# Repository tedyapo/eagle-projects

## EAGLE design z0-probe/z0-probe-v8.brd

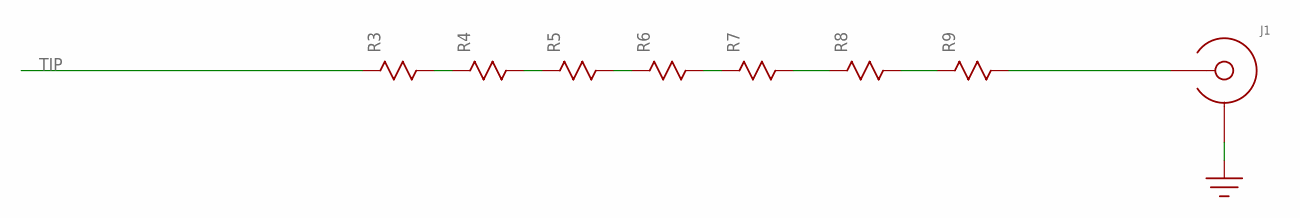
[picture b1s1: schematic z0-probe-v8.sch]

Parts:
J1: SMA-EDGE-LAUNCH; SMA_EDGE_LAUNCH_2L_4020_TAPER_FIXED
R3, R4, R5, R6, R7, R8, R9: R0603-TIGHT; 0603_TIGHT

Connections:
GND: J1.BOTTOM_GND (SHIELD), J1.GND@1 (SHIELD), J1.GND@2 (SHIELD), J1.GND@3 (SHIELD), J1.GND@4 (SHIELD), J1.GND@5 (SHIELD), J1.GND@6 (SHIELD), J1.GND@7 (SHIELD), J1.GND@8 (SHIELD), J1.GND@14 (SHIELD), J1.GND@15 (SHIELD), J1.GND@16 (SHIELD), J1.GND@17 (SHIELD), J1.GND_PAD1 (SHIELD), J1.GND_PAD2 (SHIELD), J1.P$1 (SHIELD), J1.P$2 (SHIELD)
unnamed: R3.P$2, R4.P$1
unnamed: R4.P$2, R5.P$1
unnamed: R5.P$2, R6.P$1
unnamed: R6.P$2, R7.P$1
unnamed: R7.P$2, R8.P$1
unnamed: R8.P$2, R9.P$1
unnamed: J1.CENTER@1 (CENTER), J1.P$3 (CENTER), R9.P$2
TIP: R3.P$1

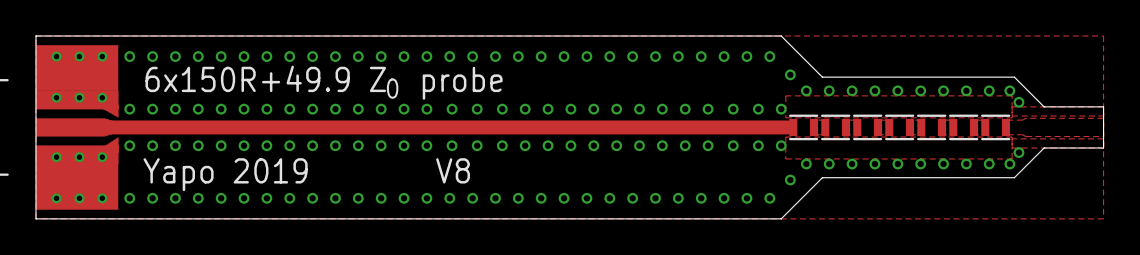
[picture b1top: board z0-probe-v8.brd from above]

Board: 2 copper layers, 59.3 x 10.2 mm, 8 parts (0 on the bottom side), 8 nets.
